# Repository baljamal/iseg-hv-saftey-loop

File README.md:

# iseg-hv-saftey-loop

PCB-based design for iseg HV power supply safety loop with filtering capacitors and bypass switches.

EDA software: KiCAD 7.0

# Note:
3D printed cover must be fabricated and mounted on safety loop board to guarantee personnel and equipment safety. \
You can find it at HV_Safety_Loop/v2/CAD

# screenshot

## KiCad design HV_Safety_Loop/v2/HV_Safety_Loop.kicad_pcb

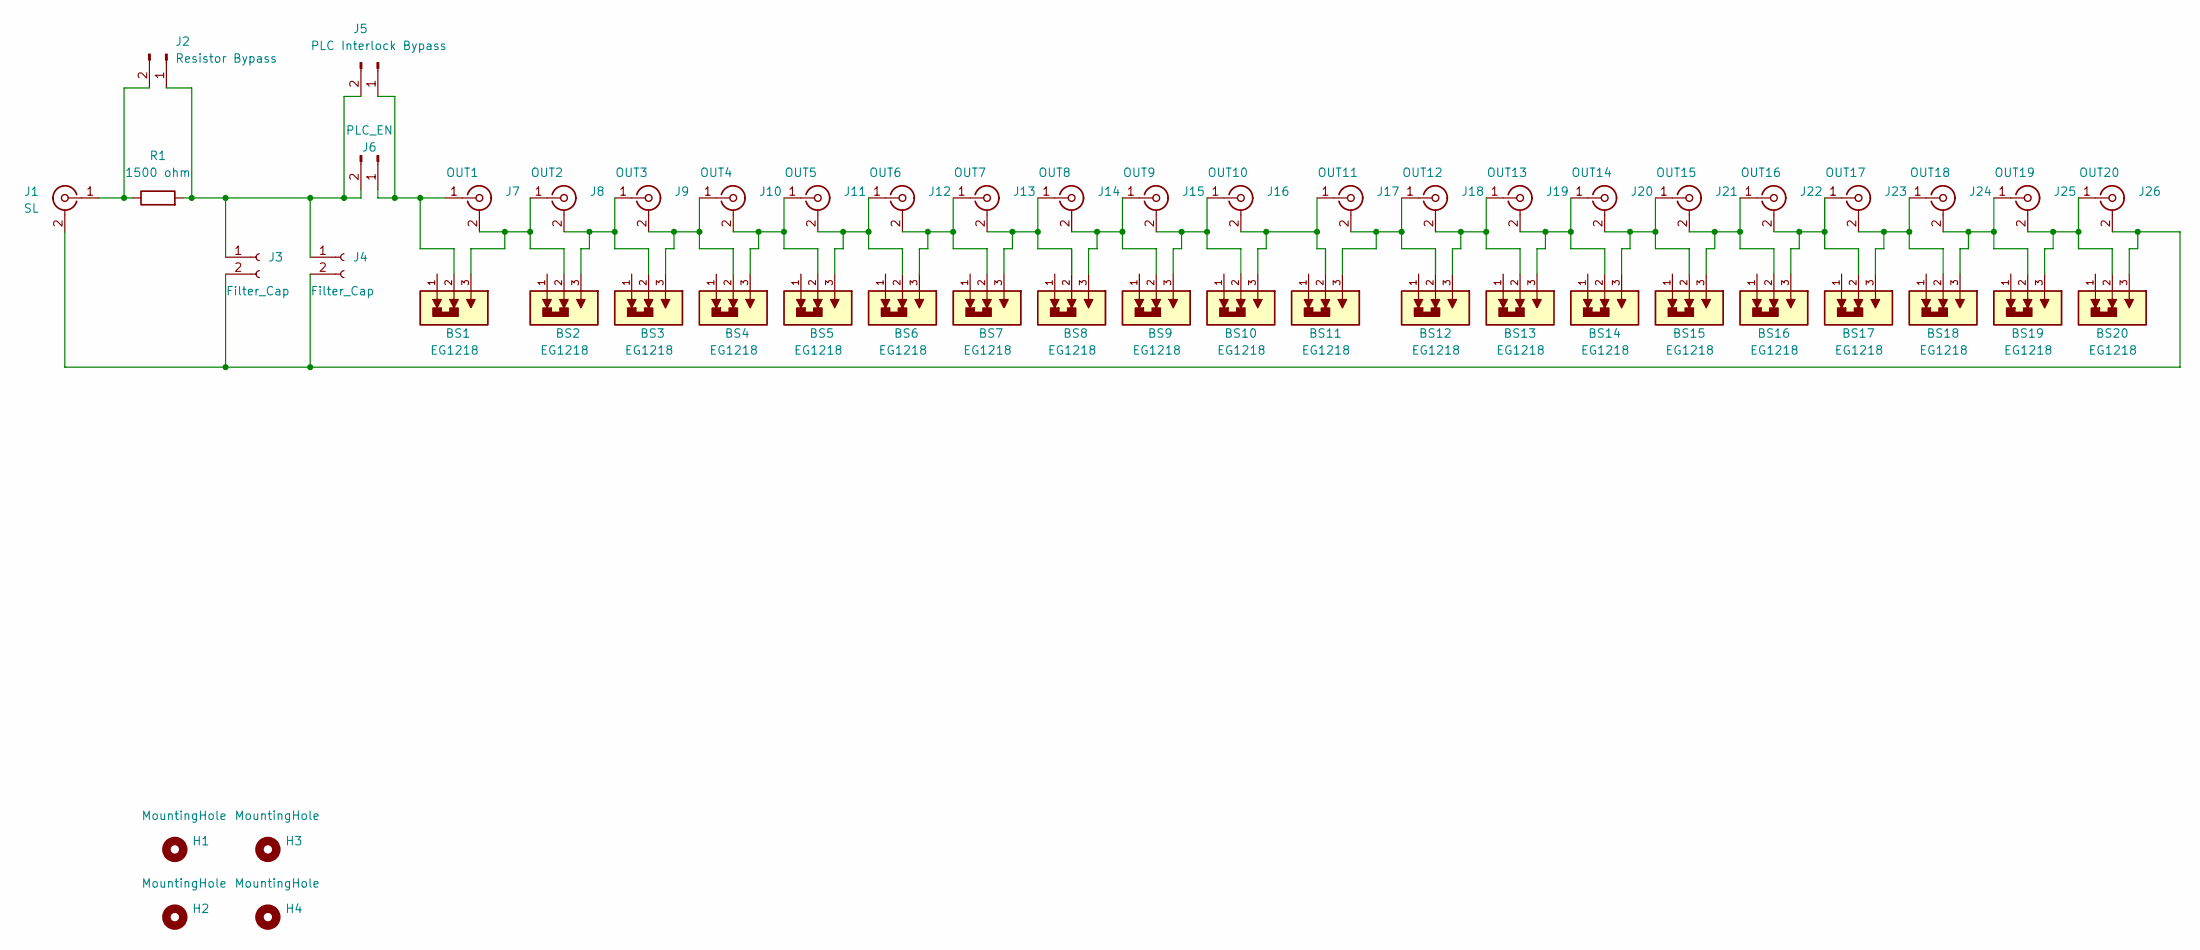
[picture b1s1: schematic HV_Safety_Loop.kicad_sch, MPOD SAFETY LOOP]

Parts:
BS1, BS2, BS3, BS4, BS5, BS6, BS7, BS8, BS9, BS10, BS11, BS12, BS13, BS14, BS15, BS16, BS17, BS18, BS19, BS20: EG1218; SW_EG1218
H1, H2, H3, H4: MountingHole; MountingHole_6.4mm_M6
J1: SL; SMB_Jack_Vertical
J2: Resistor Bypass; PinHeader_1x02_P2.54mm_Vertical
J3, J4: Filter_Cap; PinSocket_1x02_P2.54mm_Vertical
J5: PLC Interlock Bypass; PinHeader_1x02_P2.54mm_Vertical
J6: PLC_EN; PhoenixContact_MSTBA_2,5_2-G-5,08_1x02_P5.08mm_Horizontal
J7: OUT1; SMB_Jack_Vertical
J8: OUT2; SMB_Jack_Vertical
J9: OUT3; SMB_Jack_Vertical
J10: OUT4; SMB_Jack_Vertical
J11: OUT5; SMB_Jack_Vertical
J12: OUT6; SMB_Jack_Vertical
J13: OUT7; SMB_Jack_Vertical
J14: OUT8; SMB_Jack_Vertical
J15: OUT9; SMB_Jack_Vertical
J16: OUT10; SMB_Jack_Vertical
J17: OUT11; SMB_Jack_Vertical
J18: OUT12; SMB_Jack_Vertical
J19: OUT13; SMB_Jack_Vertical
J20: OUT14; SMB_Jack_Vertical
J21: OUT15; SMB_Jack_Vertical
J22: OUT16; SMB_Jack_Vertical
J23: OUT17; SMB_Jack_Vertical
J24: OUT18; SMB_Jack_Vertical
J25: OUT19; SMB_Jack_Vertical
J26: OUT20; SMB_Jack_Vertical
R1: 1500 ohm; R_2512_6332Metric

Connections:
unnamed: BS20.3, J1.2 (Ext), J3.2, J4.2, J26.2 (Ext)
unnamed: J1.1 (In), J2.2, R1.1
unnamed: J2.1, J3.1, J4.1, J5.2, J6.2, R1.2
unnamed: BS1.2, J5.1, J6.1, J7.1 (In)
unnamed: BS1.3, BS2.2, J7.2 (Ext), J8.1 (In)
unnamed: BS2.3, BS3.2, J8.2 (Ext), J9.1 (In)
unnamed: BS4.3, BS5.2, J10.2 (Ext), J11.1 (In)
unnamed: BS3.3, BS4.2, J9.2 (Ext), J10.1 (In)
unnamed: BS5.3, BS6.2, J11.2 (Ext), J12.1 (In)
unnamed: BS6.3, BS7.2, J12.2 (Ext), J13.1 (In)
unnamed: BS7.3, BS8.2, J13.2 (Ext), J14.1 (In)
unnamed: BS8.3, BS9.2, J14.2 (Ext), J15.1 (In)
unnamed: BS9.3, BS10.2, J15.2 (Ext), J16.1 (In)
unnamed: BS10.3, BS11.2, J16.2 (Ext), J17.1 (In)
unnamed: BS11.3, BS12.2, J17.2 (Ext), J18.1 (In)
unnamed: BS12.3, BS13.2, J18.2 (Ext), J19.1 (In)
unnamed: BS13.3, BS14.2, J19.2 (Ext), J20.1 (In)
unnamed: BS14.3, BS15.2, J20.2 (Ext), J21.1 (In)
unnamed: BS15.3, BS16.2, J21.2 (Ext), J22.1 (In)
unnamed: BS16.3, BS17.2, J22.2 (Ext), J23.1 (In)
unnamed: BS17.3, BS18.2, J23.2 (Ext), J24.1 (In)
unnamed: BS18.3, BS19.2, J24.2 (Ext), J25.1 (In)
unnamed: BS19.3, BS20.2, J25.2 (Ext), J26.1 (In)

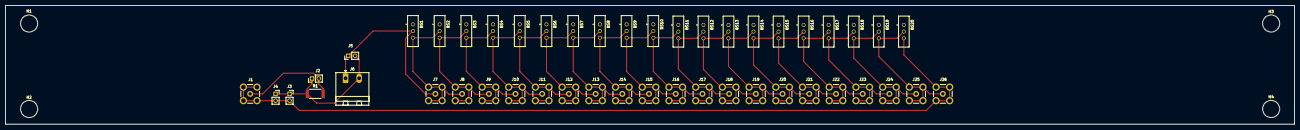
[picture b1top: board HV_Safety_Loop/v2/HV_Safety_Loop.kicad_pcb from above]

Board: 2 copper layers, 482.6 x 44.5 mm, 51 parts (0 on the bottom side), 23 nets.

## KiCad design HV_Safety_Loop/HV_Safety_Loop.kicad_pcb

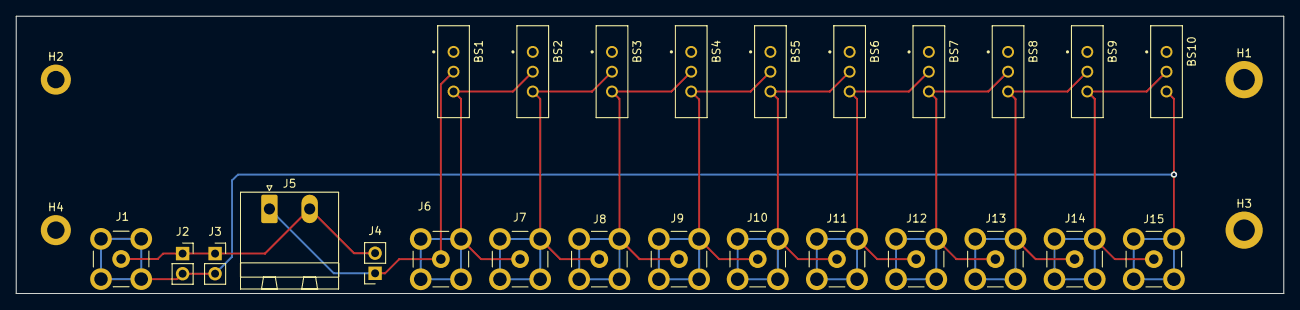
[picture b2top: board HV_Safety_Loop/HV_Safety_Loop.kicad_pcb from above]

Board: 2 copper layers, 160.0 x 35.0 mm, 29 parts (0 on the bottom side), 12 nets.

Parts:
BS1, BS2, BS3, BS4, BS5, BS6, BS7, BS8, BS9, BS10: EG1218; SW_EG1218
H1, H3: MountingHole; MountingHole_2.7mm_M2.5_DIN965_Pad
H2, H4: MountingHole; MountingHole_2.2mm_M2_DIN965_Pad
J1: SL; SMB_Jack_Vertical
J2, J3, J4: Filter_Cap; PinSocket_1x02_P2.54mm_Vertical
J5: PLC_EN; PhoenixContact_MSTBA_2,5_2-G-5,08_1x02_P5.08mm_Horizontal
J6: OUT1; SMB_Jack_Vertical
J7: OUT2; SMB_Jack_Vertical
J8: OUT3; SMB_Jack_Vertical
J9: OUT4; SMB_Jack_Vertical
J10: OUT5; SMB_Jack_Vertical
J11: OUT6; SMB_Jack_Vertical
J12: OUT7; SMB_Jack_Vertical
J13: OUT8; SMB_Jack_Vertical
J14: OUT9; SMB_Jack_Vertical
J15: OUT10; SMB_Jack_Vertical

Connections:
unnamed: BS10.3, J1.2 (Ext), J2.2, J3.2, J15.2 (Ext)
unnamed: J1.1 (In), J2.1, J3.1, J4.2, J5.2
unnamed: BS1.2, J4.1, J5.1, J6.1 (In)
unnamed: BS1.3, BS2.2, J6.2 (Ext), J7.1 (In)
unnamed: BS2.3, BS3.2, J7.2 (Ext), J8.1 (In)
unnamed: BS3.3, BS4.2, J8.2 (Ext), J9.1 (In)
unnamed: BS5.3, BS6.2, J10.2 (Ext), J11.1 (In)
unnamed: BS4.3, BS5.2, J9.2 (Ext), J10.1 (In)
unnamed: BS6.3, BS7.2, J11.2 (Ext), J12.1 (In)
unnamed: BS7.3, BS8.2, J12.2 (Ext), J13.1 (In)
unnamed: BS8.3, BS9.2, J13.2 (Ext), J14.1 (In)
unnamed: BS9.3, BS10.2, J14.2 (Ext), J15.1 (In)

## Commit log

2025-06-25 fix standoff hole size
2026-04-14 push version 2 which has 20 outputs and can fit on 19 inch rack
2026-06-29 add 3D printed cover CAD files
2026-06-29 Update README.md
    update screenshot. add 3D printed cover note
